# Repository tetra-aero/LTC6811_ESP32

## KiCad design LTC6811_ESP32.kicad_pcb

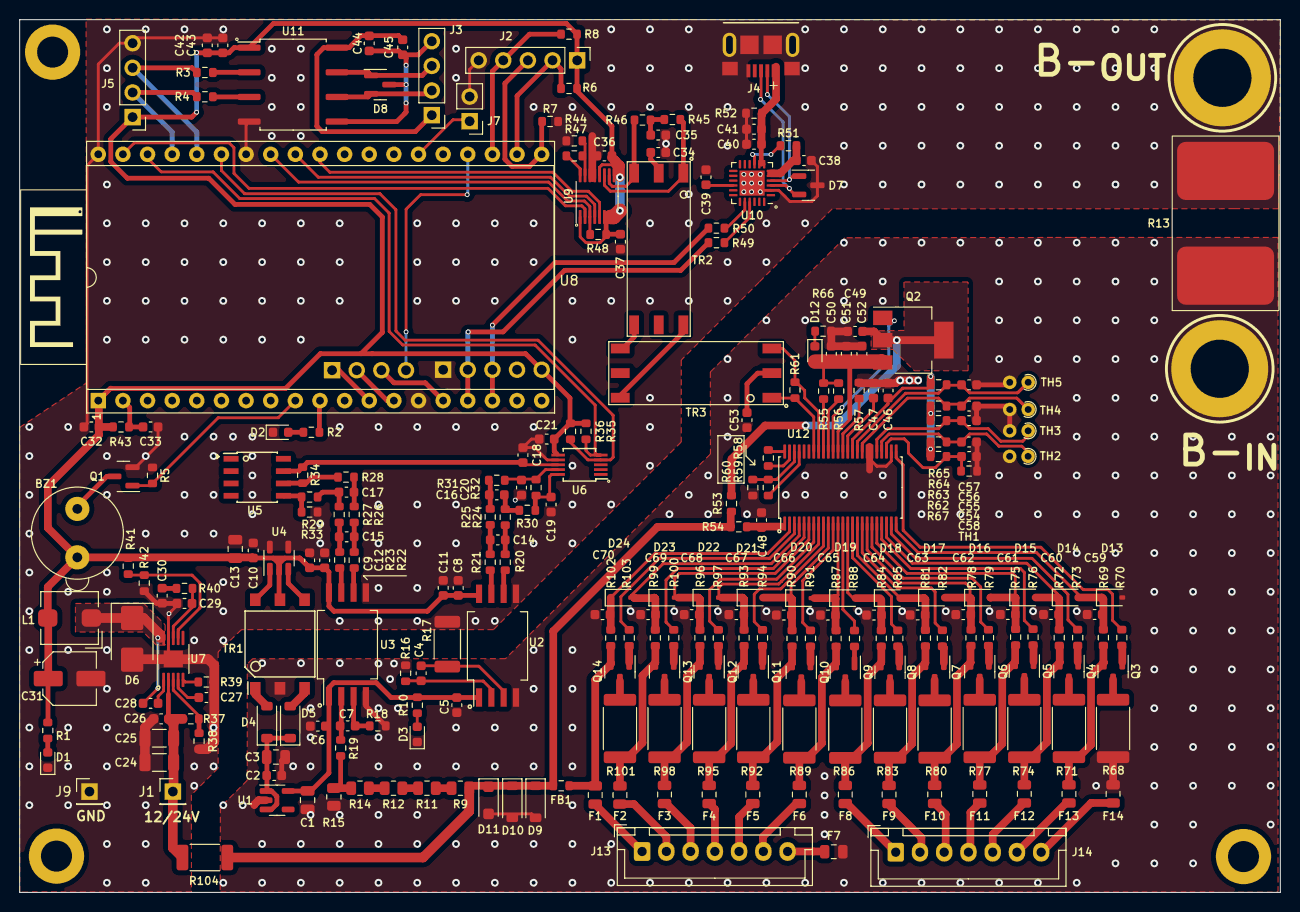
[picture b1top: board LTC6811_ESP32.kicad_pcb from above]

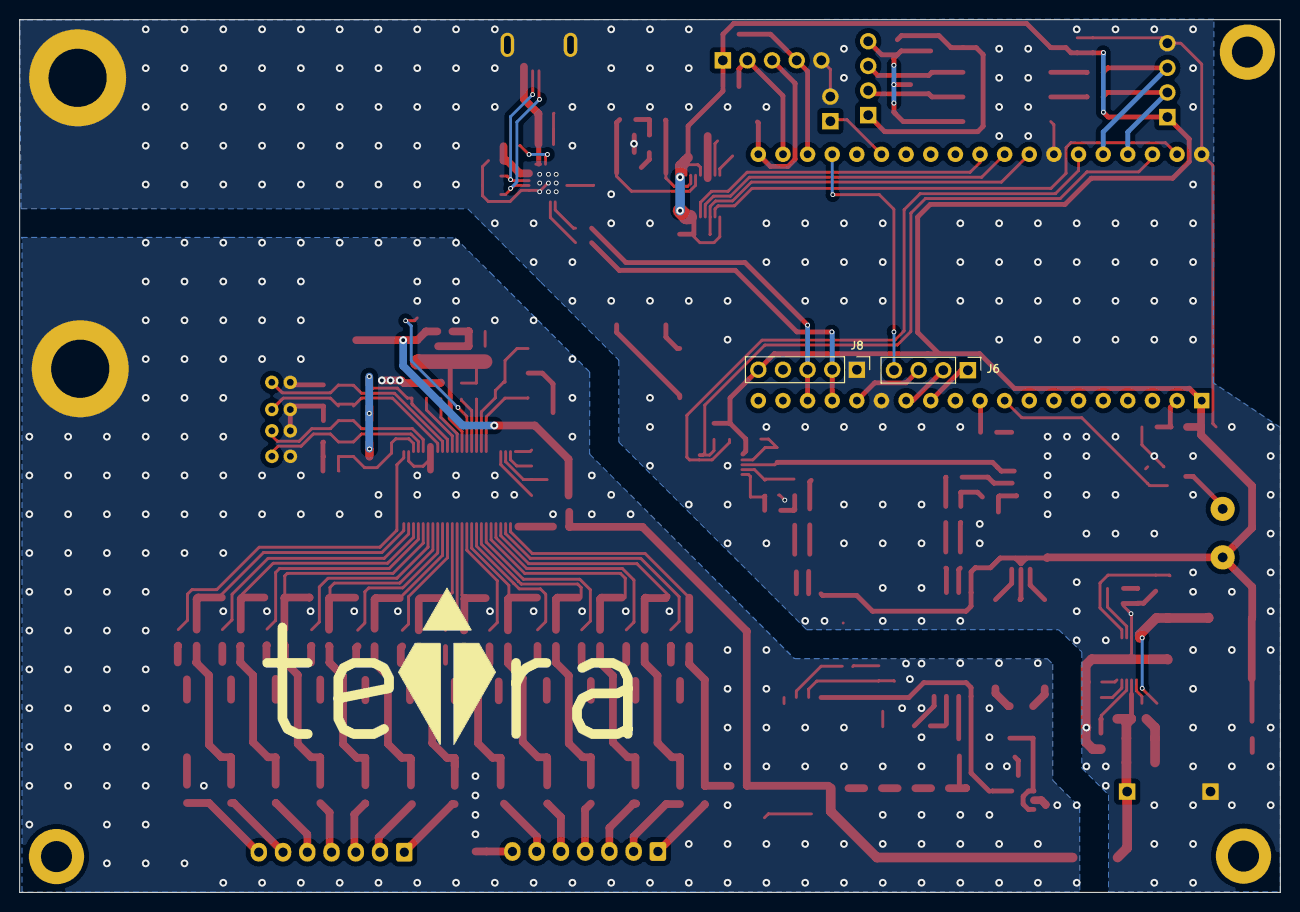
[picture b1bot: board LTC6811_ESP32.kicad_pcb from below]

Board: 2 copper layers, 130.0 x 90.0 mm, 264 parts (3 on the bottom side), 187 nets.

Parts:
BAT1: BAT-; Battery_6mm×10mm_Cell_half_2
BAT-1: BAT-; Battery_6mm×10mm_Cell_half_2
BZ1: AI-1027-TWT-5V; BUZZER
C1, C3, C13: 10uF 25V; C_0805_2012Metric
C2, C5, C6, C8, C9, C10, C18, C19, C20, C21, C26, C28, C37, C40, C43, C48, C49, C54, C55, C56, C57, C58, C59, C60, C61, C62, C63, C64, C65, C66, C67, C68, C69, C70: 100nF 100V; C_0603_1608Metric
C4, C7: 330pF 100V; C_0603_1608Metric
C11, C12, C38, C39, C41: 2.2uF 16V; C_0603_1608Metric
C14, C15: 2.2nF 16V; C_0603_1608Metric
C16, C17: 220pF 50V; C_0603_1608Metric
C24, C25: 2.2uF 100V; C_1206_3216Metric
C27, C34, C35: 10nF 100V; C_0603_1608Metric
C29: 6.8pF 50V; C_0603_1608Metric
C30: 3nF 16V; C_0603_1608Metric
C31: 47uF 16V; CP_Elec_5x4.4
C32, C33, C45: 100nF 50V; C_0603_1608Metric
C36, C42, C44, C46, C47, C50, C51, C52: 1uF 25V; C_0603_1608Metric
C53: 100pF 100V; C_0603_1608Metric
D1, D2, D3, D12: LED Red; LED_0603_1608Metric
D4, D5: MBR0520; D_SOD-123
D6: P6SMB22A; D_SMB
D7, D8: ESD24VS2U; SOT-23
D9, D10: 1N4148W; D_SOD-123
D11: BZT52H-C62; D_SOD-123F
D13, D14, D15, D16, D17, D18, D19, D20, D21, D22, D23, D24: PDZ7.5B; D_SOD-323
F1, F2, F3, F4, F5, F6, F7, F8, F9, F10, F11, F12, F13, F14: MPZ2012S102ATD25; Fuse_0805_2012Metric
FB1: BLM18PG330SN1D; R_0603_1608Metric
J1: 12/24V; PinHeader_1x01_P2.54mm_Vertical
J2: OLED /NC; PinHeader_1x05_P2.54mm_Vertical
J3: CAN /NC; PinHeader_1x04_P2.54mm_Vertical
J4: USB; Micro_USB_B-2013499-1
J5: UART /NC; PinHeader_1x04_P2.54mm_Vertical
J6: JTAG /NC; PinHeader_1x04_P2.54mm_Vertical
J7: Boot Option /NC; PinHeader_1x02_P2.54mm_Vertical
J8: SERIAL /NC; PinHeader_1x05_P2.54mm_Vertical
J9: GND; PinHeader_1x01_P2.54mm_Vertical
J10, J11, J12: Hole /NC; MountingHole_3.2mm_M3_ISO7380_Pad
J13, J14: B7B-XH-A; JST_XH_B7B-XH-A_1x07_P2.50mm_Vertical_BAT_6S
L1: 10uH; L_Bourns_SRP5030T
LOGO1: teTra /NC; teTra-LOGO
Q1: BSS138; SOT-23
Q2: NSV1C201MZ4; SOT-223
Q3, Q4, Q5, Q6, Q7, Q8, Q9, Q10, Q11, Q12, Q13, Q14: TSM2323; SOT-23
R1, R2, R10: 470R; R_0603_1608Metric
R3, R4, R55, R57: 0; R_0603_1608Metric
R5: 1.5K; R_0603_1608Metric
R6, R7, R8, R35, R36: 4.7K; R_0603_1608Metric
R9, R11, R12, R14: 470KΩ ±0.1% 250mW; R_0805_2012Metric
R13: 0.1MR 1% 15W; R_PSR500HTQFB0L10_Metric_Pad5.2x8.75mm_HandSolder
R15: 1KΩ ±0.1% 250mW; R_0805_2012Metric
R16, R18, R24, R25, R26, R27, R32: 1K; R_0603_1608Metric
R17: 1K; R_2010_5025Metric
R19: 10R; R_0603_1608Metric
R20, R21, R22, R23, R53, R54, R61, R69, R72, R75, R78, R81, R84, R87, R90, R93, R96, R99, R102: 100R; R_0603_1608Metric
R28, R29: 5.6K; R_0603_1608Metric
R30, R31, R70, R73, R76, R79, R82, R85, R88, R91, R94, R97, R100, R103: 3.3K; R_0603_1608Metric
R33, R34: 33K; R_0603_1608Metric
R37: 332K; R_0603_1608Metric
R38: 61.9K; R_0603_1608Metric
R39: 90.9K; R_0603_1608Metric
R40: 68K; R_0603_1608Metric
R41: 31.6K; R_0603_1608Metric
R42, R43, R51, R52: 10K; R_0603_1608Metric
R44, R60: 806R; R_0603_1608Metric
R45, R46: 51R; R_0603_1608Metric
R47, R59, R66: 1.2K; R_0603_1608Metric
R48: 2K; R_0603_1608Metric
R49, R50: 240R; R_0603_1608Metric
R56: 1M; R_0603_1608Metric
R58, R62, R63, R64, R65, R67: 100K; R_0603_1608Metric
R68, R71, R74, R77, R80, R83, R86, R89, R92, R95, R98, R101: 36R 1W 2512; R_2512_6332Metric
R104: 0R 2010; R_2010_5025Metric
TH1: 100K NTC; R_0603_1608Metric
TH2, TH3, TH4, TH5: 100K NTC; R_Axial_DIN0204_L3.6mm_D1.6mm_P1.90mm_Vertical
TR1: TRANSF5; WURTH-760390014
TR2, TR3: HM2108NL
U1: TPS76350; SOT-23-5
U2: AMC1301 or AMC1302; SSO-8_6.8x5.9mm_P1.27mm_Clearance8mm
U3: AMC1301; SSO-8_6.8x5.9mm_P1.27mm_Clearance8mm
U4: SN6501DBV; SOT-23-5
U5: OPA2197IDR; SOIC-8_3.9x4.9mm_Pitch1.27mm
U6: ISL28022; MSOP-10_3x3mm_P0.5mm
U7: TPS54160ADGQ; MSOP-10-1EP_3x3mm_P0.5mm_EP1.73x1.98mm
U8: ESP32-DevKitC V4; ESP32-DevKitc V4_DIP-38_27.9mm×48.2mm
U9: LTC6820; MSOP-16_3x4mm_P0.5mm
U10: CP2104; HVQFN-24-1EP_4x4mm_P0.5mm_EP2.6x2.6mm
U11: ISO1050DUBR; SOP-8_6.62x9.15mm_P2.54mm
U12: LTC6811HG-1; TSSOP-48_6.1x12.5mm_P0.5mm

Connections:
+3V3: BZ1.1 (-), C8.1, C9.1, C10.1, C11.1, C12.1, C13.1, C21.2, C31.1, C32.2, C36.2, C37.1, C42.1, C43.1, J2.1, J5.1, J8.5, L1.2, R1.2, R6.2, R8.2, R35.1, R36.1, R41.1, R43.1, R48.1, TR1.5, U2.8 (VDD2), U3.8 (VDD2), U4.2 (VCC), U6.6 (Vs), U8.1 (3V3), U9.1 (EN), U9.6 (Vcc0), U9.7 (POL), U9.8 (PHA), U9.9 (VCC), U9.12 (MSTR), U11.1 (Vcc1)
/BAT+: D9.1 (K), D10.1 (K), D11.1 (K), FB1.1, R9.1, R53.1, R54.1, R104.2
/CAN/5V_CAN: C44.1, C45.2, J3.1, U11.8 (Vcc2)
/CAN/CANH: D8.2 (K), J3.2, U11.6 (CANL)
/CAN/CANL: D8.1 (K), J3.3, U11.7 (CANH)
/CAN/CAN_GND: C44.2, C45.1, D8.3 (A), J3.4, U11.5 (GND2)
/CAN/CAN_RX: R3.2, U11.2 (RXD)
/CAN/CAN_TX: R4.2, U11.3 (TXD)
/LTC6811/C1: F13.1, J14.1 (Pin_2)
/LTC6811/C1_G: F14.1, J14.0 (Pin_1)
/LTC6811/C2: F12.1, J14.2 (Pin_3)
/LTC6811/C2_G: F7.1, J13.0 (Pin_1)
/LTC6811/C3: F11.1, J14.3 (Pin_4)
/LTC6811/C4: F10.1, J14.4 (Pin_5)
/LTC6811/C5: F9.1, J14.5 (Pin_6)
/LTC6811/C6: F8.1, J14.6 (Pin_7)
/LTC6811/C7: F6.1, J13.1 (Pin_2)
/LTC6811/C8: F5.1, J13.2 (Pin_3)
/LTC6811/C9: F4.1, J13.3 (Pin_4)
/LTC6811/C10: F3.1, J13.4 (Pin_5)
/LTC6811/C11: F2.1, J13.5 (Pin_6)
/LTC6811/C12: F1.1, J13.6 (Pin_7)
/LTC6811/DRIVE: Q2.1 (B), U12.38 (DRIVE)
/LTC6811/IMA: R61.2, TR3.3, U12.41 (IMA)
/LTC6811/IPA: R61.1, TR3.1, U12.42 (IPA)
/LTC6811/T1: C58.1, R67.2, TH1.1, U12.27 (GPIO1)
/LTC6811/T2: C54.1, R62.1, TH2.1, U12.28 (GPIO2)
/LTC6811/T3: C55.1, R63.1, TH3.1, U12.29 (GPIO3)
/LTC6811/T4: C56.1, R64.1, TH4.1, U12.32 (GPIO4)
/LTC6811/T5: C57.1, R65.1, TH5.1, U12.33 (GPIO5)
/LTC6811/Vref2: C46.1, R62.2, R63.2, R64.2, R65.2, R67.1, U12.34 (Vref2)
/LTC6811/Vreg: C50.1, C51.1, C52.1, D12.2 (A), Q2.3 (E), R55.2, R56.2, U12.37 (Vreg)
/LTC6811/cell1/C: C59.1, D13.1 (K), D14.2 (A), R69.1, U12.24 (C1)
/LTC6811/cell1/C+: F13.2, Q3.2 (S), R69.2, R71.1
/LTC6811/cell1/S: R70.1, U12.25 (S1)
/LTC6811/cell2/C: C60.1, D14.1 (K), D15.2 (A), R72.1, U12.22 (C2)
/LTC6811/cell2/C+: F12.2, Q4.2 (S), R72.2, R74.1
/LTC6811/cell2/S: R73.1, U12.23 (S2)
/LTC6811/cell3/C: C61.1, D15.1 (K), D16.2 (A), R75.1, U12.20 (C3)
/LTC6811/cell3/C+: F11.2, Q5.2 (S), R75.2, R77.1
/LTC6811/cell3/S: R76.1, U12.21 (S3)
/LTC6811/cell4/C: C62.1, D16.1 (K), D17.2 (A), R78.1, U12.18 (C4)
/LTC6811/cell4/C+: F10.2, Q6.2 (S), R78.2, R80.1
/LTC6811/cell4/S: R79.1, U12.19 (S4)
/LTC6811/cell5/C: C63.1, D17.1 (K), D18.2 (A), R81.1, U12.16 (C5)
/LTC6811/cell5/C+: F9.2, Q7.2 (S), R81.2, R83.1
/LTC6811/cell5/S: R82.1, U12.17 (S5)
/LTC6811/cell6/C: C64.1, D18.1 (K), D19.2 (A), R84.1, U12.14 (C6)
/LTC6811/cell6/C+: F8.2, Q8.2 (S), R84.2, R86.1
/LTC6811/cell6/S: R85.1, U12.15 (S6)
/LTC6811/cell7/C: C65.1, D19.1 (K), D20.2 (A), R87.1, U12.12 (C7)
/LTC6811/cell7/C+: F6.2, Q9.2 (S), R87.2, R89.1
/LTC6811/cell7/S: R88.1, U12.13 (S7)
/LTC6811/cell8/C: C66.1, D20.1 (K), D21.2 (A), R90.1, U12.10 (C8)
/LTC6811/cell8/C+: F5.2, Q10.2 (S), R90.2, R92.1
/LTC6811/cell8/S: R91.1, U12.11 (S8)
/LTC6811/cell9/S: R94.1, U12.9 (S9)
/LTC6811/cell10/C: C68.1, D22.1 (K), D23.2 (A), R96.1, U12.6 (C10)
/LTC6811/cell10/C+: F3.2, Q12.2 (S), R96.2, R98.1
/LTC6811/cell10/C-: F4.2, Q11.2 (S), R93.2, R95.1
/LTC6811/cell10/CM: C67.1, D21.1 (K), D22.2 (A), R93.1, U12.8 (C9)
/LTC6811/cell10/S: R97.1, U12.7 (S10)
/LTC6811/cell11/C: C69.1, D23.1 (K), D24.2 (A), R99.1, U12.4 (C11)
/LTC6811/cell11/C+: F2.2, Q13.2 (S), R99.2, R101.1
/LTC6811/cell11/S: R100.1, U12.5 (S11)
/LTC6811/cell12/C: C70.1, D24.1 (K), R102.1, U12.2 (C12)
/LTC6811/cell12/C+: F1.2, FB1.2, Q14.2 (S), R102.2
/LTC6811/cell12/S: R103.1, U12.3 (S12)
/MA: TR2.6, TR3.6
/MCU/BUZZER: Q1.1 (G), R5.2, U8.9 (IO25)
/MCU/Boot: J7.1, U8.25 (IO0)
/MCU/CAN_RX: J5.3, R3.1, U8.34 (RXD0)
/MCU/CAN_TX: J5.2, R4.1, U8.35 (TXD0)
/MCU/LED0: R2.2, U8.10 (IO26)
/MCU/MISO: R48.2, U8.31 (IO19), U9.3 (MISO)
/MCU/MOSI: U8.37 (IO23), U9.2 (MOSI)
/MCU/MTCK: J6.3, U8.15 (IO13)
/MCU/MTDI: J6.2, U8.13 (IO12)
/MCU/MTDO: J6.4, U8.23 (IO15)
/MCU/MTMS: J6.1, U8.12 (IO14)
/MCU/NRST: C33.2, R43.2, U8.2 (EN)
/MCU/OLED_RST: J2.3, R7.2, U8.20 (CLK)
/MCU/OLED_SCL: J2.4, R8.1, U8.22 (SD1)
/MCU/OLED_SDA: J2.2, R6.1, U8.21 (SD0)
/MCU/RX_USB: J8.2, R49.2, U8.16 (SD2)
/MCU/SCK: U8.30 (IO18), U9.4 (SCK)
/MCU/SCL: R35.2, U6.5 (SCL), U8.36 (IO22)
/MCU/SDA: R36.2, U6.4 (SDA), U8.33 (IO21)
/MCU/SS: U8.29 (IO5), U9.5 (CSB)
/MCU/TX_USB: J8.3, R50.2, U8.17 (SD3)
/PA: TR2.4, TR3.4
/PowerMonitor/ISO+5V: C1.1, C5.1, C6.1, R10.2, U1.5 (VOUT), U2.1 (VDD1), U3.1 (VDD1)
/PowerMonitor/Vbat: C18.2, R34.2, U5.7, U6.8 (Vbus)
/PowerSupply/12/24V: C24.1, C25.1, C26.2, J1.1, R37.1, R104.1, U7.2 (VIN)
/USB/D+: D7.2 (K), J4.3 (D+), U10.3 (D+)
/USB/D-: D7.1 (K), J4.2 (D-), U10.4 (D-)
/USB/Vusb: C40.1, C41.1, J4.1 (VBUS), R52.1, U10.7 (REGIN), U10.8 (VBUS)
GND: BAT-1.1, C8.2, C9.2, C10.2, C11.2, C12.2, C13.2, C18.1, C19.1, C20.1, C21.1, C24.2, C25.2, C26.1, C27.2, C29.2, C30.2, C31.2, C32.1, C33.1, C34.2, C35.1, C36.1, C37.2, C38.2, C39.2, C40.2, C41.2, C42.2, C43.2, D1.1 (K), D2.1 (K), D6.2 (A), D7.3 (A), J2.5, J4.5 (GND), J4.6 (Shield), J5.4, J7.2, J8.1, J9.1, Q1.2 (S), R5.1, R7.1, R13.2, R17.1, R33.2, R38.2, R39.2, R42.2, R44.2, R52.2, U2.5 (GND2), U3.5 (GND2), U4.4 (GND), U4.5 (GND), U6.7 (GND), U7.9 (GND), U7.11 (PGND), U8.14 (GND), U8.32 (GND), U8.38 (GND), U9.13 (SLOW), U9.14 (GND), U10.2 (GND), U10.25 (PAD), U11.4 (GND1)
GND_PACK: BAT1.1, C1.2, C2.2, C3.2, C5.2, C6.2, C46.2, C47.2, C48.2, C49.2, C50.2, C51.2, C52.2, C53.2, C54.2, C55.2, C56.2, C57.2, C58.2, C59.2, C60.2, C61.2, C62.2, C63.2, C64.2, C65.2, C66.2, C67.2, C68.2, C69.2, C70.2, D3.1 (K), D9.2 (A), D10.2 (A), D11.2 (A), D13.2 (A), F7.2, F14.2, R13.1, R15.2, R16.1, R18.2, R57.2, R60.2, R66.2, R68.1, TH1.2, TH2.2, TH3.2, TH4.2, TH5.2, TR1.2, U1.2 (GND), U2.4 (GND2), U3.4 (GND2), U12.26 (C0), U12.30 (V-**), U12.31 (V-)
unnamed: BZ1.2 (+), Q1.3 (D)
unnamed: C14.1, R20.1, R24.1
unnamed: C14.2, R21.1, R25.1
unnamed: C15.1, R22.1, R26.1
unnamed: C15.2, R23.1, R27.1
unnamed: C16.1, R24.2, R30.2
unnamed: C16.2, R25.2, R31.2
unnamed: C17.1, R26.2, R28.1
unnamed: C17.2, R27.2, R29.1
unnamed: C30.1, R40.2
unnamed: C34.1, TR2.2
unnamed: C35.2, R45.1, R46.2
unnamed: C49.1, Q2.2 (C), Q2.4 (C), R53.2
unnamed: C53.1, TR3.2
unnamed: D1.2 (A), R1.1
unnamed: D2.2 (A), R2.1
unnamed: D3.2 (A), R10.1
unnamed: D4.2 (A), TR1.1
unnamed: C2.1, C3.1, D4.1 (K), D5.1 (K), U1.1 (VIN), U1.3 (EN)
unnamed: D5.2 (A), TR1.3
unnamed: C28.2, D6.1 (K), L1.1, U7.10 (PH)
unnamed: D12.1 (K), R66.1
unnamed: Q3.3 (D), R68.2
unnamed: Q3.1 (G), R70.2
unnamed: Q4.3 (D), R71.2
unnamed: Q4.1 (G), R73.2
unnamed: Q5.3 (D), R74.2
unnamed: Q5.1 (G), R76.2
unnamed: Q6.3 (D), R77.2
unnamed: Q6.1 (G), R79.2
unnamed: Q7.3 (D), R80.2
unnamed: Q7.1 (G), R82.2
unnamed: Q8.3 (D), R83.2
unnamed: Q8.1 (G), R85.2
unnamed: Q9.3 (D), R86.2
unnamed: Q9.1 (G), R88.2
unnamed: Q10.3 (D), R89.2
unnamed: Q10.1 (G), R91.2
unnamed: Q11.3 (D), R92.2
unnamed: Q11.1 (G), R94.2
unnamed: Q12.3 (D), R95.2
unnamed: Q12.1 (G), R97.2
unnamed: Q13.3 (D), R98.2
unnamed: Q13.1 (G), R100.2
unnamed: Q14.3 (D), R101.2
unnamed: Q14.1 (G), R103.2
unnamed: R9.2, R11.1
unnamed: R11.2, R12.1
unnamed: R12.2, R14.1
unnamed: R14.2, R15.1, R19.1
unnamed: C4.2, R17.2, U2.3 (VINN)
unnamed: C4.1, R16.2, U2.2 (VINP)
unnamed: R20.2, U2.6 (VOUTN)
unnamed: R21.2, U2.7 (VOUTP)
unnamed: C7.2, R18.1, U3.3 (VINN)
unnamed: C7.1, R19.2, U3.2 (VINP)
unnamed: R22.2, U3.6 (VOUTN)
unnamed: R23.2, U3.7 (VOUTP)
unnamed: TR1.6, U4.1 (D1)
unnamed: TR1.4, U4.3 (D2)
unnamed: R29.2, R33.1, U5.5 (+)
unnamed: R28.2, R34.1, U5.6 (-)
unnamed: C19.2, R30.1, R32.1, U6.10 (Vin+)
unnamed: C20.2, R31.1, R32.2, U6.9 (Vin-)
unnamed: C28.1, U7.1 (BOOT)
unnamed: C29.1, R40.1, U7.8 (COMP)
unnamed: R37.2, R38.1, U7.3 (EN)
unnamed: R39.1, U7.5 (RT/CLK)
unnamed: C27.1, U7.4 (SS/TR)
unnamed: R41.2, R42.1, U7.7 (VSENSE)
unnamed: R47.1, U9.16 (IBIAS)
unnamed: R44.1, R47.2, U9.15 (ICMP)
unnamed: R46.1, TR2.3, U9.10 (IM)
unnamed: R45.2, TR2.1, U9.11 (IP)
unnamed: R50.1, U10.20 (RXD)
unnamed: R49.1, U10.21 (TXD)
unnamed: C39.1, U10.16 (VPP)
unnamed: R51.2, U10.9 (~RST)
unnamed: R57.1, U12.36 (DTEN)
unnamed: R59.1, U12.45 (IBIAS)
unnamed: R59.2, R60.1, U12.46 (ICMP)
unnamed: R58.1, U12.47 (IMB)
unnamed: R58.2, U12.48 (IPB)
unnamed: R55.1, U12.40 (ISOMD)
unnamed: C48.1, R54.2, U12.1 (V+)
unnamed: C47.1, U12.35 (Vref1)
unnamed: R56.1, U12.39 (WDT)
VDD: C38.1, R51.1, U10.5 (VIO), U10.6 (VDD)

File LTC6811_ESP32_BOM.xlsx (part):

LTC6811_ESP32_BOM
NO. | Reference | Value | Footprint | Datasheet | Description | Link | MPN | Quantity
1 | BZ1 | AI-1027-TWT-5V | ENNOID:BUZZER | https://www.puiaudio.com/media/SpecSheet/AI-1027-TWT-5V-2-R.pdf | Buzzers Indicator, Internally Driven Electromechanical/Magnetic 5 V 30mA 2.73kH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 | https://www.digikey.jp/en/products/detail/pui-audio-inc/AI-1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 | AI-1027-TWT-5V-2-R | 1
2 | C1, C3, C13 | 10uF 25V | Capacitor_SMD:C_0805_2012Metric | https://mm.digikey.com/Volume0/opasdata/d220001/medias/docus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 | 10 uF ±10% 25V Ceramic Capacitor X5R 0805 (2012 Metric) | https://www.digikey.jp/en/products/detail/samsung-electro-me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 | CL21A106KAYNNNE | 3
3 | C2, C5, C6, C8-C10, C18-C21, C26, C28, C37, C40, C43, C48, C49, C54-C70 | 100nF 100V | Capacitor_SMD:C_0603_1608Metric | https://www.digikey.jp/en/products/detail/samsung-electro-me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 | 0.1 uF ±10% 100V Ceramic Capacitor X7R 0603 (1608 Metric) | https://www.digikey.jp/en/products/detail/samsung-electro-me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 | CL10B104KC8NNNC | 34
4 | C4, C7 | 330pF 100V | Capacitor_SMD:C_0603_1608Metric | https://www.digikey.jp/en/products/detail/murata-electronics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 | 330 pF ±10% 100V Ceramic Capacitor X7R 0603 (1608 Metric) | https://search.murata.co.jp/Ceramy/image/img/A01X/G101/ENG/G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 | GRM188R72A331KA01D | 2
5 | C11, C12, C38, C39, C41 | 2.2uF 16V | Capacitor_SMD:C_0603_1608Metric | https://connect.kemet.com:7667/gateway/IntelliData-Component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 | 2.2 uF ±10% 16V Ceramic Capacitor X5R 0603 (1608 Metric) | https://www.digikey.jp/en/products/detail/kemet/C0603C225K4P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 | C0603C225K4PAC7867 | 5
6 | C14, C15 | 2.2nF 16V | Capacitor_SMD:C_0603_1608Metric | https://connect.kemet.com:7667/gateway/IntelliData-Component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 | 2200 pF ±10% 16V Ceramic Capacitor X7R 0603 (1608 Metric) | https://www.digikey.jp/en/products/detail/kemet/C0603C222K4R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 | C0603C222K4RECAUTO | 2
7 | C16, C17 | 220pF 50V | Capacitor_SMD:C_0603_1608Metric | https://search.murata.co.jp/Ceramy/image/img/A01X/G101/ENG/G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 | 220 pF ±5% 50V Ceramic Capacitor C0G, NP0 0603 (1608 Metric) | https://www.digikey.jp/en/products/detail/murata-electronics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 | GCM1885C1H221JA16D | 2
8 | C24, C25 | 2.2uF 100V | Capacitor_SMD:C_1206_3216Metric | https://www.samsungsem.com/resources/file/global/support/pro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 | 2.2 uF ±10% 100V Ceramic Capacitor X7R 1206 (3216 Metric) | https://www.digikey.jp/en/products/detail/samsung-electro-me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 | CL31B225KCHSNNE | 2
9 | C27, C34, C35 | 10nF 100V | Capacitor_SMD:C_0603_1608Metric | https://search.murata.co.jp/Ceramy/image/img/A01X/G101/ENG/G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 | 10000 pF ±10% 100V Ceramic Capacitor X7R 0603 (1608 Metric) | https://www.digikey.jp/en/products/detail/murata-electronics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 | GCM188R72A103KA37D | 3
10 | C29 | 6.8pF 50V | Capacitor_SMD:C_0603_1608Metric | https://datasheets.kyocera-avx.com/C0GNP0-KGM.pdf | 6.8 pF ±0.5pF 50V Ceramic Capacitor C0G, NP0 0603 (1608 Metric) | https://www.digikey.jp/en/products/detail/kyocera-avx/KGM15A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 | KGM15ACG1H6R8DT | 1
11 | C30 | 3nF 16V | Capacitor_SMD:C_0603_1608Metric | https://www.digikey.jp/en/products/detail/kemet/C0603C333J4R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 | 0.033 uF ±5% 16V Ceramic Capacitor X7R 0603 (1608 Metric) | https://connect.kemet.com:7667/gateway/IntelliData-Component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 | C0603C333J4REC7411 | 1
12 | C31 | 47uF 16V | Capacitor_SMD:CP_Elec_5x4.4 | https://industrial.panasonic.com/cdbs/www-data/pdf/AAB8000/A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 | 47 uF 16 V Aluminum - Polymer Capacitors Radial, Can - SMD 25mOhm 5000 Hrs @ 10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 | https://www.digikey.jp/en/products/detail/panasonic-electron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 | 16SVPG47M | 1
13 | C32, C33, C45 | 100nF 50V | Capacitor_SMD:C_0603_1608Metric | https://mm.digikey.com/Volume0/opasdata/d220001/medias/docus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 | 0.1 uF ±10% 50V Ceramic Capacitor X7R 0603 (1608 Metric) | https://www.digikey.jp/en/products/detail/nextgen-components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 | 0603B104K500XD | 3
14 | C36, C42, C44, C46, C47, C50-C52 | 1uF 25V | Capacitor_SMD:C_0603_1608Metric | https://mm.digikey.com/Volume0/opasdata/d220001/medias/docus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 | 1 uF ±10% 25V Ceramic Capacitor X7R 0603 (1608 Metric) | https://www.digikey.jp/en/products/detail/nextgen-components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 | 0603B105K250XD | 8
15 | C22,C53 | 100pF 100V | Capacitor_SMD:C_0603_1608Metric | https://mm.digikey.com/Volume0/opasdata/d220001/medias/docus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 | 100 pF ±10% 100V Ceramic Capacitor X7R 0603 (1608 Metric) | https://www.digikey.jp/en/products/detail/nextgen-components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 | 0603B101K101SD | 2
16 | D1-D3, D12 | LED Red | LED_SMD:LED_0603_1608Metric | https://optoelectronics.liteon.com/upload/download/DS-22-99-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 | Red 631nm LED Indication - Discrete 2V 0603 (1608 Metric) | https://www.digikey.jp/en/products/detail/liteon/LTST-C190KR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 | LTST-C190KRKT | 4
17 | D4, D5 | MBR0520 | Diode_SMD:D_SOD-123 | http://www.mccsemi.com/up_pdf/MBR0520~MBR0580(SOD123).pdf | Diode 20 V 500mA Surface Mount SOD-123 | https://www.digikey.jp/en/products/detail/micro-commercial-c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 | MBR0520-TP | 2
18 | D6 | P6SMB22A | Diode_SMD:D_SMB | https://mm.digikey.com/Volume0/opasdata/d220001/medias/docus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 | 30.6V Clamp 19.9A Ipp Tvs Diode Surface Mount SMB (DO-214AA) | https://www.digikey.jp/en/products/detail/bourns-inc/P6SMB22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 | P6SMB22A | 1
19 | D7, D8 | ESD24VS2U | Package_TO_SOT_SMD:SOT-23 | https://www.infineon.com/dgdl/Infineon-ESD24VS2U-DS-v01_01-e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 | 41V Clamp 5A (8/20us) Ipp Tvs Diode Surface Mount PG-SOT23 | https://www.digikey.jp/en/products/detail/infineon-technolog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 | ESD24VS2UE6327HTSA1 | 2
20 | D9, D10 | 1N4148W | Diode_SMD:D_SOD-123 | https://www.diodes.com/assets/Datasheets/BAV16W_1N4148W.pdf | Diode 100 V 300mA Surface Mount SOD-123 | https://www.digikey.jp/en/products/detail/diodes-incorporate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 | 1N4148W-7-F | 2
21 | D11 | BZT52H-C62 | Diode_SMD:D_SOD-123F | https://assets.nexperia.com/documents/data-sheet/BZT52H_SER.pdf | Zener Diode 62 V 375 mW ±5% Surface Mount SOD-123F | https://www.digikey.jp/en/products/detail/nexperia-usa-inc/B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 | BZT52H-C62,115 | 1
22 | D13-D24 | PDZ7.5B | Diode_SMD:D_SOD-323 | https://assets.nexperia.com/documents/data-sheet/PDZ-B_SER.pdf | Zener Diode 7.6 V 400 mW ±2% Surface Mount SOD-323 | https://www.digikey.jp/en/products/detail/nexperia-usa-inc/P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 | PDZ7.5BZ | 12
23 | F1-F14 | MPZ2012S102ATD25 | Fuse:Fuse_0805_2012Metric | https://product.tdk.com/en/system/files?file=dam/doc/product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 | 1 kOhms @ 100 MHz 1 Power Line Ferrite Bead 0805 (2012 Metric) 1.5A 150mOhm | https://www.digikey.jp/en/products/detail/tdk-corporation/MP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 | MPZ2012S102ATD25 | 14
24 | FB1 | BLM18PG330SN1D | Resistor_SMD:R_0603_1608Metric | https://www.murata.com/en-us/products/productdata/8796738650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 | 33 Ohms @ 100 MHz 1 Power Line Ferrite Bead 0603 (1608 Metric) 3A 25mOhm | https://www.digikey.jp/en/products/detail/murata-electronics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 | BLM18PG330SN1D | 1
25 | J2 | OLED /NC | Connector_PinHeader_2.54mm:PinHeader_1x05_P2.54mm_Vertical | https://tools.molex.com/pdm_docs/sd/705430001_sd.pdf | Connector Header Through Hole 5 position 0.100" (2.54mm) | https://www.digikey.jp/en/products/detail/molex/0705430004/1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 | 70543-0004 | 1
26 | J3 | CAN /NC | Connector_PinHeader_2.54mm:PinHeader_1x04_P2.54mm_Vertical | https://suddendocs.samtec.com/prints/tsw-xxx-xx-x-x-xx-xxx-f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 | Connector Header Through Hole 4 position 0.100" (2.54mm) | https://www.digikey.jp/en/products/detail/samtec-inc/TSW-104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 | TSW-104-07-G-S | 1
27 | J4 | USB | Connector_USB:Micro_USB_B-2013499-1 | https://www.te.com/usa-en/product-2013499-1.datasheet.pdf | USB - micro B USB 2.0 Receptacle Connector 5 Position Surface Mount, Right Angl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 | https://www.digikey.jp/en/products/detail/te-connectivity-am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 | 2013499-1 | 1
28 | J5 | UART /NC | Connector_PinHeader_2.54mm:PinHeader_1x04_P2.54mm_Vertical | https://suddendocs.samtec.com/prints/tsw-xxx-xx-x-x-xx-xxx-f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 | Connector Header Through Hole 4 position 0.100" (2.54mm) | https://www.digikey.jp/en/products/detail/samtec-inc/TSW-104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 | TSW-104-07-G-S | 0
29 | J6 | JTAG /NC | Connector_PinHeader_2.54mm:PinHeader_1x04_P2.54mm_Vertical | https://suddendocs.samtec.com/prints/tsw-xxx-xx-x-x-xx-xxx-f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 | Connector Header Through Hole 4 position 0.100" (2.54mm) | https://www.digikey.jp/en/products/detail/samtec-inc/TSW-104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 | TSW-104-07-G-S | 0
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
